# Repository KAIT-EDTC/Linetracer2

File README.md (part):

# Linetracer2 — 子ども向け教材ライントレーサー（Lite rev.L5）

> 最終更新: 2026-11-19（**Lite に一本化**。以前の「標準版 rev.A1」（Raspberry Pi Pico ＋ LBR-123F ×6）は削除した。git の履歴（コミット `3216870` まで）に残っている）
> 基板は **rev.L5**（2026-11-19: **回路を全部見直した**（§0）。車輪を止めたときにモータードライバの定格 2.0 A を超えないようにソフトでモーターを平均 1.6 V までに、売っていない昇降圧モジュール AE-TPS63802 を **AE-XC9306-5V0** に（向きをまちがえられない）、電池のばねが一瞬離れても XIAO が落ちないように **C2 470 µF**。1 台 約 ¥171 安く）。その前の rev.L4（2026-10-30）はモーターに力がかかると XIAO が落ちる問題を 5 V 昇降圧モジュールで直した版（§0b）。**未製造・未試作**。
> **KiCad のファイル（回路図・基板・Gerber・PDF・絵）、手順の絵、ロボット全体の 3D と干渉チェックは rev.L5 で作り直した**（KiCad 10.0.8、ERC 0・DRC 0（警告も 0）・未接続 0・回路図との不一致 0、干渉なし、2026-11-19）。
> マイコン **Seeed Studio XIAO ESP32C6**（ピンヘッダで付ける）、センサー **LBR-127HLD ×3**、モータードライバー **TC78H653FTG**（秋月モジュール）、**130 モーター ×2** と 3D プリントのギヤボックス（1 段 5:1）、**ブザー**、**フルカラー LED 6 こ**、**テストパッド**、XIAO 用の **5 V 昇降圧モジュール（AE-XC9306-5V0）**。配線は全部手で引いた（交差なし・ビア 0）。前の支えは**ボールキャスター**（§1）。
> **全部足付き部品（スルーホール）で子どもが自分ではんだ付けできる**。テープ・接着剤は使わず、M3 ねじと 3D プリントのツメで組み立てる。部品は秋月・ホームセンター・タミヤ品など、**T 番号のある店で買える定番品だけ**（`docs/bom.md` §0）。
> 回路図: `hardware/kicad/Linetracer2-Lite.kicad_sch`（PDF: `docs/Linetracer2-Lite_schematic.pdf`）
> 製造データ: `hardware/Linetracer2-Lite_rev.L5_gerber.zip`（発注のしかた §4.10。rev.L3・rev.L4 の Gerber は消した。git の履歴に残っている）　ソフト: `firmware/micropython/`（Arduino C++ 版: [`firmware/arduino/`](firmware/arduino/README.md)）　組み立て手順書: [`docs/assembly.md`](docs/assembly.md)
> **ロボット全体の 3D モデル**: `hardware/Linetracer2-Lite_assembly.stl`（GitHub 上でそのまま回して見られる）、色つき `hardware/Linetracer2-Lite_assembly.glb`。部品付き基板だけの STEP: `hardware/kicad/Linetracer2-Lite_pcb.step`
> 前の版 rev.L2（XIAO じか付け、自動配線）は git の履歴とプルリクエスト #3 に、rev.L1（Pico ＋ LBR-123F）はコミット `1db5a53` に残っている。

| ロボット全体（3D） | 横から |
|---|---|
|  |  |

| 基板の上面（3D） | 裏面（3D、センサー面） |
|---|---|
|  |  |

| シルク（表。子どもが読む印刷） | シルク（裏、下から見た向き） |
|---|---|
|  |  |

## ドキュメント

| ファイル | 内容 |
|---------|------|
| この README | 設計書（依頼と結論・変更点と理由・回路・基板・部品表・ソフト・作り直し方・まだ確かめていないこと） |
| [docs/assembly.md](docs/assembly.md) | 組み立て手順書（基板の記号の見かた、つくる順番 ①〜⑰、機械の組み立て、うごかしかた） |
| [docs/bom.md](docs/bom.md) | 部品表（秋月のリンクつき）、買い方のルール、10 台分の注文リスト |
| [docs/drivetrain.md](docs/drivetrain.md) | 駆動系の計算（モーター・ギヤ比・速さ・電流）と電池 |
| [docs/08_knowledge.md](docs/08_knowledge.md) | 知見メモ（部品のクセ、買い方、KiCad / OpenSCAD のハマりどころ、設計判断） |
| [hardware/mechanical/README.md](hardware/mechanical/README.md) | 3D プリント部品と P1S の印刷設定、ねじ、干渉チェック |
| [hardware/Linetracer2-Lite_print_set.zip](hardware/Linetracer2-Lite_print_set.zip) | 1 台分の STL を印刷設定ごとのフォルダに分けた zip |
| [docs/Linetracer2-Lite_schematic.pdf](docs/Linetracer2-Lite_schematic.pdf) | 回路図 PDF（組立図: `docs/Linetracer2-Lite_assembly_top.pdf` / `_bottom.pdf`） |
| [docs/datasheets/README.md](docs/datasheets/README.md) | 使った部品のデータシート（リンク集） |

## フォルダ構成

```
Linetracer2/
├── README.md                 設計書（このファイル）
├── docs/                     手順書・部品表・知見メモ、回路図/組立図 PDF、基板とロボットの画像、手順ごとの絵（steps/）
├── hardware/
│   ├── kicad/                KiCad 10 プロジェクト（Linetracer2-Lite.kicad_pro / _sch / _pcb）、自作ライブラリ（lib/）、BOM、ERC/DRC
│   ├── gerber/               製造用 Gerber・ドリル
│   ├── Linetracer2-Lite_rev.L5_gerber.zip   ← 基板メーカーにそのまま渡す
│   ├── Linetracer2-Lite_assembly.stl / .glb ロボット全体の 3D
│   ├── Linetracer2-Lite_print_set.zip       3D プリント 1 台分
│   └── mechanical/           3D プリント部品（OpenSCAD 元データ、STL、図）
├── firmware/
│   ├── micropython/          ライブラリ・標準プログラム・授業用サンプル（XIAO ESP32C6 用 MicroPython）
│   └── arduino/              Arduino（C++）版のライブラリとスケッチ
└── scripts/                  回路図・基板・3D モデルを作り直すスクリプト（§9）
```

---

## 0. rev.L5（2026-11-19）: 回路を全部見直した（落ちない・こわれない・安く）

依頼「モーターを最大で回したときなどに不具合が起きないか。いまの昇降圧（でんげん モジュール）で大丈夫か。もっと安くできないか（電池を 1 本増やすだけでも変わるかも）。落ちないようにする工夫。LED の抵抗の付け忘れや、電流を食いすぎてモーターの電圧が下がるような所がないか。子どもがフラフラ（ゆらす・つかむ・ぶつける）してもマイコンがプツンと落ちない、電子回路として正しく動く、いらない部品は削ってよい、いちばん安全で、値段もおさえた回路に」への答え。

**結論**: 回路の形（電池 3 本 → モーター、電池 → D1 → 5 V 昇降圧 → D8 → XIAO）はそのままでよい。直すべき所が 3 つあった: **① 車輪を止めるとドライバの定格を超える電流が流れる**（ソフトの上限で直した）、**② でんげん モジュールが売っていない**（同じ働きで安く、向きをまちがえられないモジュールに替えた）、**③ 電池のばねが一瞬離れると XIAO が落ちる**（電気だめのコンデンサを足した）。1 台 **約 ¥171 安く**なった（約 ¥3,360）。電池を 4 本にする案は、かえって落ちやすく高くつくのでやめた（§0.4）。

### 0.1 見つかったことと、したこと

| # | 見つかったこと | どうなるか | rev.L5 |
|---|---|---|---|
| 1 | **モーターの「100 %」は平均 3.0 V。車輪を手で止める・壁に当たると約 2.6 A**（止まったモーターは逆起電力が無く、電流 = 電圧 ÷ 約 0.9 Ω）。ドライバ TC78H653FTG（スモールモード）の**絶対最大定格は 2.0 A**（10 ms までなら 2.5 A）。過電流検出（ISD）のしきい値はデータシートでも「参考値・保証しない」（VM 3〜4 V で 2〜3 A）ので、**働かないまま 2.0〜3 A が流れ続ける**ことがある。ソフトは 0.1 秒ごとに ISD を解除するので、止めている間ずっとくり返す | ドライバがこわれる・熱くなる。モーターも 4.6 W で熱くなる。電池が 2.5 V まで下がる | **ソフトの上限 `MAX_MOTOR_VOLT` を 3.0 → 1.6 V**（MicroPython・Arduino とも）。止めても**最大約 1.75 A**（定格の 9 割弱）。**電池から出る電流も半分**になり、電池の電圧の落ちこみも半分。速さは理論 2.7 m/s で十分（3 センサーで実際に走れるのは 1 m/s 前後）。速さレベルと Kp・Kd を合わせ直した（`docs/drivetrain.md` §3） |
| 2 | **でんげん モジュール AE-TPS63802 が秋月で「入荷未定」、店も通販も在庫 0**（2026-11-19。値段も 2026-01 に ¥660 → ¥780）。さらに、VR1 の代わりの 470 kΩ を付ける前に電気を入れると**こわれる**準備が要り、4 ピン 1 列なので**裏返しでも差さる** | 授業の 10 台がそろわない。先生の準備でこわしやすい | **AE-XC9306-5V0（秋月 115775、¥600、在庫 386）に替えた**。同じ同期整流の昇降圧で **5 V 固定**（入力 2.5〜5.5 V、3.3 V 入力で 500 mA）。準備は付属の細ピンヘッダを付けて **TRIM のピンを 1 本抜くだけ**。**基板に TRIM の穴を開けない**ので、モジュールは**正しい向きでしか入らない**（裏返しても回しても入らない → 入力と出力を入れかえられない）。20 × 13 mm → 8.5 × 7.6 mm |
| 3 | 電池ボックスのばねは、ぶつけたりゆらしたりすると**一瞬（〜数 ms）離れる**。VSYS（= USB の VBUS）は USB の決まり（10 µF まで）で大きいコンデンサを置けず、電気だめが 40 µF ほどしかない（0.5 ms） | 子どもがゆらす・ぶつけると XIAO が「プツン」とリセットしうる | **C2 470 µF を D1 のうしろ（モジュールの入力 VIN_BB）に足した**。D1 があるのでモーターには吸われず、USB の VBUS でもない。約 3 ms もつ（モジュールは 2.5 V まで動く）。**C1 と同じ部品**で、⑮ でいっしょに付ける（部品の種類は増えない、+¥10） |
| 4 | フルカラー LED は明るさ 255 で 6 こ 0.36 A。**XIAO の Wi-Fi の次に 5 V を食う**。子どもがソフトで 255 にすると、電池が減ったときにモジュールの出せる電流（2.5 V 入力で約 0.3 A）が足りなくなる | 電池が減ると XIAO が落ちる | ソフトで明るさを**最大 100（6 こ白で 0.14 A）に固定**（`RGB_LIMIT`、MicroPython・Arduino。標準は今までどおり 60） |
| 5 | **LED の抵抗の付け忘れ** | — | **無かった**。赤外 LED（センサーの中）は 100 Ω で約 20 mA（最大 60 mA）。フルカラー LED は中に定電流回路があるので抵抗は要らない（R11 は信号線の保護、§3.6）。XIAO の LED は XIAO の中で抵抗付き。トランジスタのベース（R7 1 kΩ）・ブザー（R9 100 Ω）・ボタン（R10 1 kΩ）も OK |
| 6 | **電流を食いすぎて、モーターの電圧を下げている所** | — | **無かった**（§0.3）。モーター以外は全部で電池から 0.15〜0.7 A（Wi-Fi のとき多い）。モーターの電圧が下がる原因は電池の内部抵抗とモーター自身の電流（1 で半分にした） |
| 7 | 電池を逆に付ける（J1 を逆にはんだ付け）と、ドライバの中のダイオードで電池がショート | ドライバがこわれる・電池が熱くなる | 変わらず（足付きで 3 V で ON する MOSFET が秋月に無い、PTC は止めたときの電流で切れる・電圧が下がる）。**XH コネクタは逆に差せない形**、手順書 ⑩ で先生が向きを見る。D1 が XIAO とモジュールは守る |
| 8 | 手順の絵を作る `scripts/step_images.py` が、Lite をリポジトリの直下に移したあとも古い場所（`lite/docs/steps`）に書こうとして失敗していた（`export_assembly.sh` のパイプで失敗が隠れていた） | 手順の絵・3D が古いまま | 直して、失敗が隠れないようにした。**手順の絵・ロボット全体の 3D・干渉チェックを rev.L5 で作り直した**（rev.L3 のままだった） |

**いらない部品**: **470 kΩ（U3 の準備用）がいらなくなった**。ほかの部品はどれも役目がある（§0.5）ので残した。

### 0.2 モーターを止めたとき、電池の電圧はどこまで下がるか（計算）

電池（新品アルカリ 3 本: 4.7 V・0.7 Ω（ばね・スイッチ・線をふくむ）、半分使ったアルカリ: 3.8 V・1.0 Ω、ニッケル水素: 3.9 V・0.35 Ω）、モーター＋ドライバ 0.9 Ω、XIAO などの 5 V 側 0.1 A（Wi-Fi なし）、D1 0.35 V。

| 電池 | 場面 | rev.L4（上限 3.0 V、TPS63802 は 1.3 V まで） | **rev.L5（上限 1.6 V、XC9306 は 2.5 V まで）** |
|---|---|---|---|
| 新品アルカリ | 片方の車輪を止める | 電池 3.3 V・**モーター 2.6 A（定格超え）** | 電池 4.1 V・モーター 1.75 A |
| 新品アルカリ | 両方止める（走り出しの一瞬も近い） | 電池 2.5 V・モーター 2.0 A | 電池 3.7 V・モーター 1.6 A |
| 新品アルカリ | 両方止める＋Wi-Fi（0.3 A） | 電池 2.3 V | 電池 3.5 V（モジュールの入力 3.2 V） |
| ニッケル水素 | 片方を止める | 電池 3.2 V・**モーター 2.5 A（定格超え）** | 電池 3.6 V・モーター 1.5 A |
| ニッケル水素 | 両方止める＋Wi-Fi | 電池 2.6 V・**モーター 2.1 A（定格超え）** | 電池 3.3 V（入力 3.0 V） |
| 半分使ったアルカリ | 片方を止める | 電池 2.2 V（入力 1.9 V で動く） | 電池 3.1 V（入力 2.7 V で動く） |
| 半分使ったアルカリ | 両方止める | 電池 1.6 V（入力 1.2 V → **XIAO が落ちる**） | 電池 2.7 V（入力 2.3 V → **XIAO が落ちる**） |

- rev.L5 は**新品アルカリ・ニッケル水素なら、両輪を止めても、Wi-Fi を使っていても落ちない**。どの場面でもドライバの定格 2.0 A を超えない。
- 半分使ったアルカリで両輪を止めると、rev.L4 と同じく落ちる（モジュールが止まる → XIAO がリセット → モーターも止まって電流が減る → 電池がもどってまた起動し、ド・ミ・ソが鳴る）。**電池を替えるサイン**。こわれはしない。
- **いちばん落ちにくいのはニッケル水素（eneloop など）**（内部抵抗が小さい）。`BATTERY_VOLT` を 3.7 に（§8.2）。
- 計算のしかた: モーターの電流 = デューティ × 電池の電圧 ÷ 0.9 Ω、電池の電流 = デューティ × モーターの電流 ＋ 5 V 側（5 V × 電流 ÷ 効率 0.85 ÷ 入力の電圧）、電池の電圧 = 開放電圧 − 内部抵抗 × 電池の電流（くり返し計算）。デューティはソフトが `MAX_MOTOR_VOLT ÷ BATTERY_VOLT`（4.2 V）で決める（電池を測れないので）。

### 0.3 どこが電流を使うか

| 使う所 | 電流 | 電源 |
|---|---|---|
| モーター 2 こ | 走っている間 1 こ 0.2〜0.7 A（電池からは合わせて 0.3〜1 A）。止めると最大 1.75 A（rev.L5） | VBAT（電池そのまま） |
| フルカラー LED 6 こ | 1 こ 待機 約 1 mA、白でいっぱいに光ると 60 mA。標準の明るさ 60/255 で 6 こ白 約 85 mA、上限 100 で 0.14 A | VSYS（5 V 側） |
| 赤外 LED 3 こ（センサー） | 20 mA × 3 = 60 mA（読むときだけ ON、外の光を消すため ON/OFF をくり返す） | 3V3（XIAO の中の降圧） |
| XIAO（ESP32-C6） | 走るだけ 約 30 mA、Wi-Fi の電波を出す瞬間 約 0.3 A | 3V3 |
| センサーのプルアップ・ボタン・ブザー | 1 mA 以下（ブザーは鳴っている間 数 mA） | 3V3 / D4 |
| **でんげん モジュール（U3）が出す 5 V** | **0.1 A（走るだけ）〜 0.4 A（Wi-Fi ＋ LED）**。出せるのは 3.3 V 入力で 0.5 A（秋月の資料、基板にじか付けのとき）。電池側では 0.15〜0.7 A | VIN_BB（D1 のあと） |

- XIAO の 3V3 は XIAO の中の降圧 DC-DC（SGM6029）が作る。赤外 LED 60 mA ＋ ESP32-C6 で十分まにあう。
- **ピンの電流**: どの GPIO も 5 mA 以下（ドライバの入力 µA、Q1 のベース 2.6 mA、ブザー 33 mA は R9 で決まる瞬間のピークで、ふだん数 mA、R11 は 5 mA 以下）。ESP32-C6 の限度（40 mA / 28 mA）の中。

### 0.4 電池を 4 本にしたら？（答え: しない）

| | 単3 ×3（いま） | 単3 ×4 |
|---|---|---|
| 電池の電圧 | 3.3〜4.8 V | 4.4〜6.4 V |
| XIAO の電源 | 5 V 昇降圧モジュールが要る（電池が 3.8 V を切ると、ダイオードだけでは XIAO が動かない） | **それでも電源の部品が要る**: XIAO の 5V ピン（= USB の VBUS）は **5.6 V でクランプ**される（Seeed の回路図）。新品アルカリ 4 本 6.4 V は高すぎ、いまのモジュール（5.5 V まで）にも入れられない → 降圧（LDO など）が要る |
| 落ちにくさ | 電池が 2.8 V まで下がっても XIAO は動く | LDO だと電池が**約 4.5 V を切ると XIAO が落ちる**（LDO の電圧降下 0.3〜0.5 V ＋ D8 ＋ XIAO の中の降圧）。半分使ったアルカリ 4 本（5.0 V・1.2 Ω）で両輪を止めると 3.9 V → **落ちる**。いまより落ちやすい |
| 部品代 | AE-XC9306-5V0 ¥600 | 低損失 LDO 50〜100 円（−¥500）。でも電池ボックス（4 本）、**デッキの作り直し**、重さ +23 g |
| 電池代 | 1 回 3 本 | 1 回 4 本（授業 10 台で毎回 +10 本） |
| モーター | — | 電圧が高い分デューティが小さくなるだけ。止めたときの電流はソフトの上限で決まるので同じ |
| 間違い | — | 子どもが 4 本のボックスに替えたまま古い基板（rev.L4 以前）を使うとこわれる |

→ 4 本にしても電源の部品は要り、落ちにくさは悪くなり、機械の作り直しと電池代が増える。**3 本＋昇降圧のまま**にした。

### 0.5 もっと安くできるか・部品を減らせるか

| 案 | 差 | 判断 |
|---|---|---|
| **でんげん モジュールを AE-XC9306-5V0 に** | −¥180（470 kΩ も不要） | **した**（§0.1 の 2） |
| C2 470 µF を足す | +¥10 | **した**（§0.1 の 3、落ちない工夫） |
| もっと安い昇圧モジュール（秋月 AE-XCL102D503CR-G ¥300 など） | −¥300 | しない。出力 0.21 A で、Wi-Fi（0.3 A の瞬間）や LED で足りない |
| マイコンを Raspberry Pi Pico 2 W に（中に 1.8〜5.5 V の昇降圧があり、電池の電圧も測れる） | XIAO ¥1,100 ＋ モジュール ¥600 → Pico 2 W 約 ¥1,500（スイッチサイエンス）で −¥200 くらい | 今回はしない。基板・ソフト（MicroPython・Arduino・Wi-Fi）を全部作り直すことになる。Wi-Fi が要らなければ Wi-Fi なしの Pico でもっと安くなる。次の世代の候補 |
| フルカラー LED を 6 → 2 こ | −¥160 | しない（依頼で 6 こにした） |
| D9・R11・C3・C4・テストパッドをやめる | −¥1〜20 | しない。D9 = LED が XIAO の 3.3 V の信号を読むため、R11 = はんだのミスで XIAO のピンがこわれないため、C3・C4 = モーターの雑音（センサー・Wi-Fi）、テストパッド = 銅だけで 0 円 |
| D1 をやめる | −¥10 | しない。電池の逆接続から XIAO とモジュールを守り、C2 をモーターから切りはなす |
| D8 をやめる | −¥10 | しない。無いと USB をつないだとき、モジュールと PC の USB が 5 V を押しあう |

### 0.6 回路（rev.L5）

```
単3×3 ─ VBAT ─┬─ モータードライバ VM（C1 470µF）。モーターは平均 1.6 V まで（ソフト）
              └─ D1 1N5819 ─ VIN_BB ─┬─ C2 470µF（電気だめ。ばねが一瞬離れても約 3 ms もつ）
                                      └─ U3 AE-XC9306-5V0（昇降圧 5.0 V、ON/OFF は空き、TRIM は穴なし）
                                           └─ VOUT_BB ─ D8 1N5819 ─ VSYS（約 4.7 V）─┬─ XIAO 5V ピン → 3.3 V
                                                                                      ├─ 右のフルカラー LED 3 こ
                                                                                      └─ D9 1N4148 ─ VLED_L（約 4.0 V）─ 左の 3 こ
              USB-C の 5 V も VSYS に来る（XIAO の中で直結）。D8 があるので U3 には流れない
```

- 配置: U3 は真ん中（rev.L4 の大きいモジュールの場所の後ろ半分）。左の列 = I（前）・G・O（うしろ）、右の列 = ON/OFF・GND・（TRIM の穴なし）。**O は D8 のアノードと同じ高さ**で 1 本の横線、**C2 の ＋ は U3 の I のまっすぐ前**で、D1 → C2 ＋ → U3 I が 1 本の線。抵抗の絵（① ちゃ ② だいだい ③ あか）は C2 の右、XIAO のアンテナの前へ移した（銅の禁止エリアだがシルクは描ける）。U3 の下には線を通さない。
- **U3 の外形とピンの位置は秋月の説明書の図から**（8.5 × 7.6 mm、ピッチ 2.54、列の間 7.6）。図の向き（裏から見たか表から見たか）を読みちがえていても、TRIM の穴が無いので「部品の面を下にした向き」でだけ入り、どのピンも正しい穴に来る。**発注の前に実物で確かめる**（§10）。
- KiCad で作り直した: ERC 0、**DRC 0（警告も 0）**、未接続 0、回路図との不一致 0（KiCad 10.0.8）。Gerber は `hardware/Linetracer2-Lite_rev.L5_gerber.zip`（rev.L4 の zip は消した）。ロボット全体の 3D と干渉チェック（`export_assembly.sh`）も rev.L5 で通した: 枠・デッキ・電池ボックス・モーター・ギヤ・キャスター・ねじ、すべて「空」。
- ソフト: MicroPython は構文チェック、Arduino は 3 つのスケッチを XIAO_ESP32C6 用にコンパイルした（esp32 3.3.11）。**実物ではまだ動かしていない**。

### 0.7 部品とコスト（1 台）

| | 変化 |
|---|---|
| U3 AE-TPS63802（¥780）→ **AE-XC9306-5V0（115775、¥600）** | −¥180 |
| 470 kΩ（VR1 の代わり）をやめた | −¥1 |
| **C2 470 µF**（C1 と同じ 108426） | +¥10 |
| **合計** | **−¥171 → 1 台 約 ¥3,360**（rev.L4 約 ¥3,531） |

はんだ付けは子どもが +3 か所（U3 は 4 → 5、C2 の 2）、先生の準備は 6 → 5 か所（細ピンヘッダ 5、抵抗なし）。

---

## 0b. rev.L4（2026-10-30）: モーターに力がかかると XIAO が落ちる → 電源を作り直した

> rev.L4 のときの記録。**rev.L5 で U3 は AE-XC9306-5V0 に替わり（470 kΩ の準備は不要）、C2 470 µF を D1 のうしろに足し、モーターの上限を 1.6 V にした**（§0）。下の U3 の説明・部品・コストは rev.L4 の AE-TPS63802 のもの。

依頼「モーターにトルクをかけたときや、モーター出力 100 % にしたときに XIAO が落ちるので回路を組み直して。ほかにも回路的に良くないところ・問題点をくまなく見て」への答え。

### 0b.1 原因: XIAO の電源が、モーターと同じ電池から「ダイオード 1 本」でとっていた

rev.L3 は `単3×3 ─ D1 ─ XIAO の 5V ピン` だった。XIAO の中は `5V ピン ─ ショットキー（約 0.3 V）─ 降圧 DC-DC ─ 3.3 V` なので、3.3 V を保つには電池の側で**約 4.0 V**、ESP32-C6 がリセットしないためにも**約 3.4 V** 要る。ところが単3 アルカリ 3 本は、モーターが大きい電流を流すとすぐその下まで下がる。

計算の前提: 電池 3 本 ＋ 電池ボックスのばね・スイッチ・線の抵抗 ≒ 0.7 Ω（新品）、FA-130RA-2270 の巻線 ≒ 0.68 Ω（1.5 V で止めると 2.2 A）、TC78H653FTG（スモールモード）のオン抵抗 0.22 Ω、ソフトの 100 % = 電池の 71 %（3.0 V ÷ 4.2 V）。

| 場面 | 電池から出る電流 | 電池の電圧（新品 4.65 V） | rev.L3 の XIAO |
|---|---|---|---|
| ふつうに走っている（2 つで 1 A くらい） | 約 1.0 A | 約 3.9 V | ぎりぎり動く |
| **片方の車輪を手で止めて 100 %**（もう片方は止まっている） | 約 1.9 A | **約 3.3 V** | **リセット** |
| **2 つとも 100 % で走り出す・2 つとも止める** | 約 2.9 A | **約 2.6 V** | **リセット** |
| （少し減った電池 3.9 V・1.2 Ω で 2 つとも止める） | 約 1.9 A | 約 1.7 V | リセット |

- 470 µF（C2）は 0.2 A で 1 ms ほどしか持たない。モーターが止まっている間（何百 ms）は支えられない。
- つまり**ソフトの問題ではなく、電源の作り方の問題**。走り出しのソフトスタート（`RAMP_PER_CALL`）は入っているが、車輪を止められると電流は減らない。
- 標準版（Pico）では起きにくい: Pico の VSYS の中に**昇降圧の DC-DC（1.8〜5.5 V）**があるから。XIAO ESP32C6 の中は降圧だけなので、Lite では外に昇降圧が要る。

### 0b.2 なおしかた: XIAO 専用の 5 V を、昇降圧モジュールで作る

```
単3×3 ─ VBAT ─┬─ モータードライバ VM（C1 470µF）
              └─ D1 1N5819 ─ VIN_BB ─ U3 AE-TPS63802（昇降圧、VR1 = 470kΩ → 5.13 V、EN = VIN）
                                        └─ VOUT_BB ─ D8 1N5819 ─ VSYS（約 4.8 V）─┬─ XIAO 5V ピン → 3.3 V
                                                                                   ├─ 右のフルカラー LED 3 こ（D5〜D7）
                                                                                   └─ D9 1N4148 ─ VLED_L（約 4.1 V）─ 左の 3 こ（D2〜D4）
              USB-C の 5 V も VSYS に来る（XIAO の中で直結）。D8 があるので U3 には流れない
```

- **U3 = 秋月 AE-TPS63802**（TI TPS63802 の昇降圧モジュールキット、¥780、20 × 13 mm、4 ピン: VIN・GND・VOUT・EN）。**入力 1.3〜5.5 V で動き続け**（はじめの起動は 1.8 V 以上）、スイッチ電流 2 A。電池が**約 1.6 V**（D1 のあとで 1.3 V）まで下がっても XIAO に 5 V を出す。上の表のいちばん悪い場面（2.6 V）でも余裕がある。
  - 昇圧だけでなく**昇降圧**なので、新品のアルカリ（4.8 V）でもニッケル水素（3.6 V）でも同じ 5.13 V。
  - 秋月で買えて、ピンヘッダで付けられて、1 A 近く出せるのはこれだけだった。もっと安い昇圧モジュール（AE-XCL102 / XCL103、5 V）は出力 0.2 A ほどで、Wi-Fi（`03_WiFiControl`）やフルカラー LED を使うと足りない。
  - 出力は VR1（25 回転の半固定抵抗）で決まる。**VR1 の代わりに 470 kΩ の抵抗を付けて 5.13 V に固定**（秋月の説明書の表の値。半固定抵抗だと回してしまう・高さがある）。**VR1 が空のまま電気を入れるとこわれる**ので、先生が先に付けて単3 ×2 本でためす（手順書 §0）。
  - EN は VIN につないで「いつも ON」（TI の注意: EN を浮かせてはいけない）。モードのジャンパーはそのまま（強制 PWM）。
- **D8**（1N5819）: XIAO の 5V ピンは USB の VBUS と直結。D8 が無いと、U3 が PC の USB に電気を押しこみ、USB の 5 V が U3 の出力に逆から入る。D8 のおかげで VSYS は約 4.8 V（USB の 5 V より少し低い）: **USB をつなぐと USB から、外すとすぐ U3 から**。
- **D1**（1N5819）はそのまま: 電池を逆につないだとき、U3 と XIAO を守る（U3 の入力は −0.3 V まで）。
- **C2（VSYS の 470 µF）はやめた**: VSYS は USB の VBUS そのもので、USB の決まりは 10 µF まで（差した瞬間の突入電流で PC のポートが落ちることがある）。U3 の出力にはモジュールのコンデンサがある。
- XIAO の 5V ピンには約 4.8 V。中の降圧 DC-DC にとって十分（3.6 V 以上あればよい）。

### 0b.3 ほかに見つけた回路の問題と対応

| # | 問題 | どうなるか | rev.L4 |
|---|---|---|---|
| 1 | **XIAO の電源が電池じか**（§0b.1） | モーターに力がかかると XIAO がリセット | **U3（5 V 昇降圧）を足した** |
| 2 | **ニッケル水素 3 本（3.6 V）だと、止まっていても足りない**（rev.L3 の説明は「NiMH は `BATTERY_VOLT` を 3.7 に」としていたが、XIAO の 3.3 V が保てない） | 不安定・動かない | U3 で解決（NiMH でも 5.13 V。内部抵抗が小さいのでモーターにはむしろよい） |
| 3 | **USB の VBUS（= VSYS）に 470 µF（C2）** | USB を差した瞬間の突入電流（規格は 10 µF まで）。PC のポートが落ちる・つながらないことがある | C2 をやめた（部品が 1 つ減った） |
| 4 | **フルカラー LED の信号の電圧が足りない**: PL9823 は VDD の 0.7 倍より高いと「1」。USB の 5 V では 3.5 V 要るが、XIAO は 3.3 V | USB だけだと光らない・色がおかしい（rev.L3 §10 で心配していたこと）。U3 で VSYS が 4.8 V に上がると電池でも同じになる | **左の 3 こ（信号が最初に入る D2 を含む）の電源を D9（1N4148）で 0.7 V 下げた**: 約 4.1 V → 2.9 V で「1」。D2〜D4 は自分の VDD（4.1 V）で次へ信号を渡すので、右の 3 こ（4.8 V → 3.4 V）にも足りる |
| 5 | フルカラー LED の電源が電池 − D1（新品で約 4.2 V）で、決まり（4.5〜6 V）より低い | 電池が減ると青と緑が暗くなる | 右の 3 こは 4.8 V（決まりの中）。左の 3 こは 4.1 V（rev.L3 と同じくらい、でも電池が減っても変わらない） |
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
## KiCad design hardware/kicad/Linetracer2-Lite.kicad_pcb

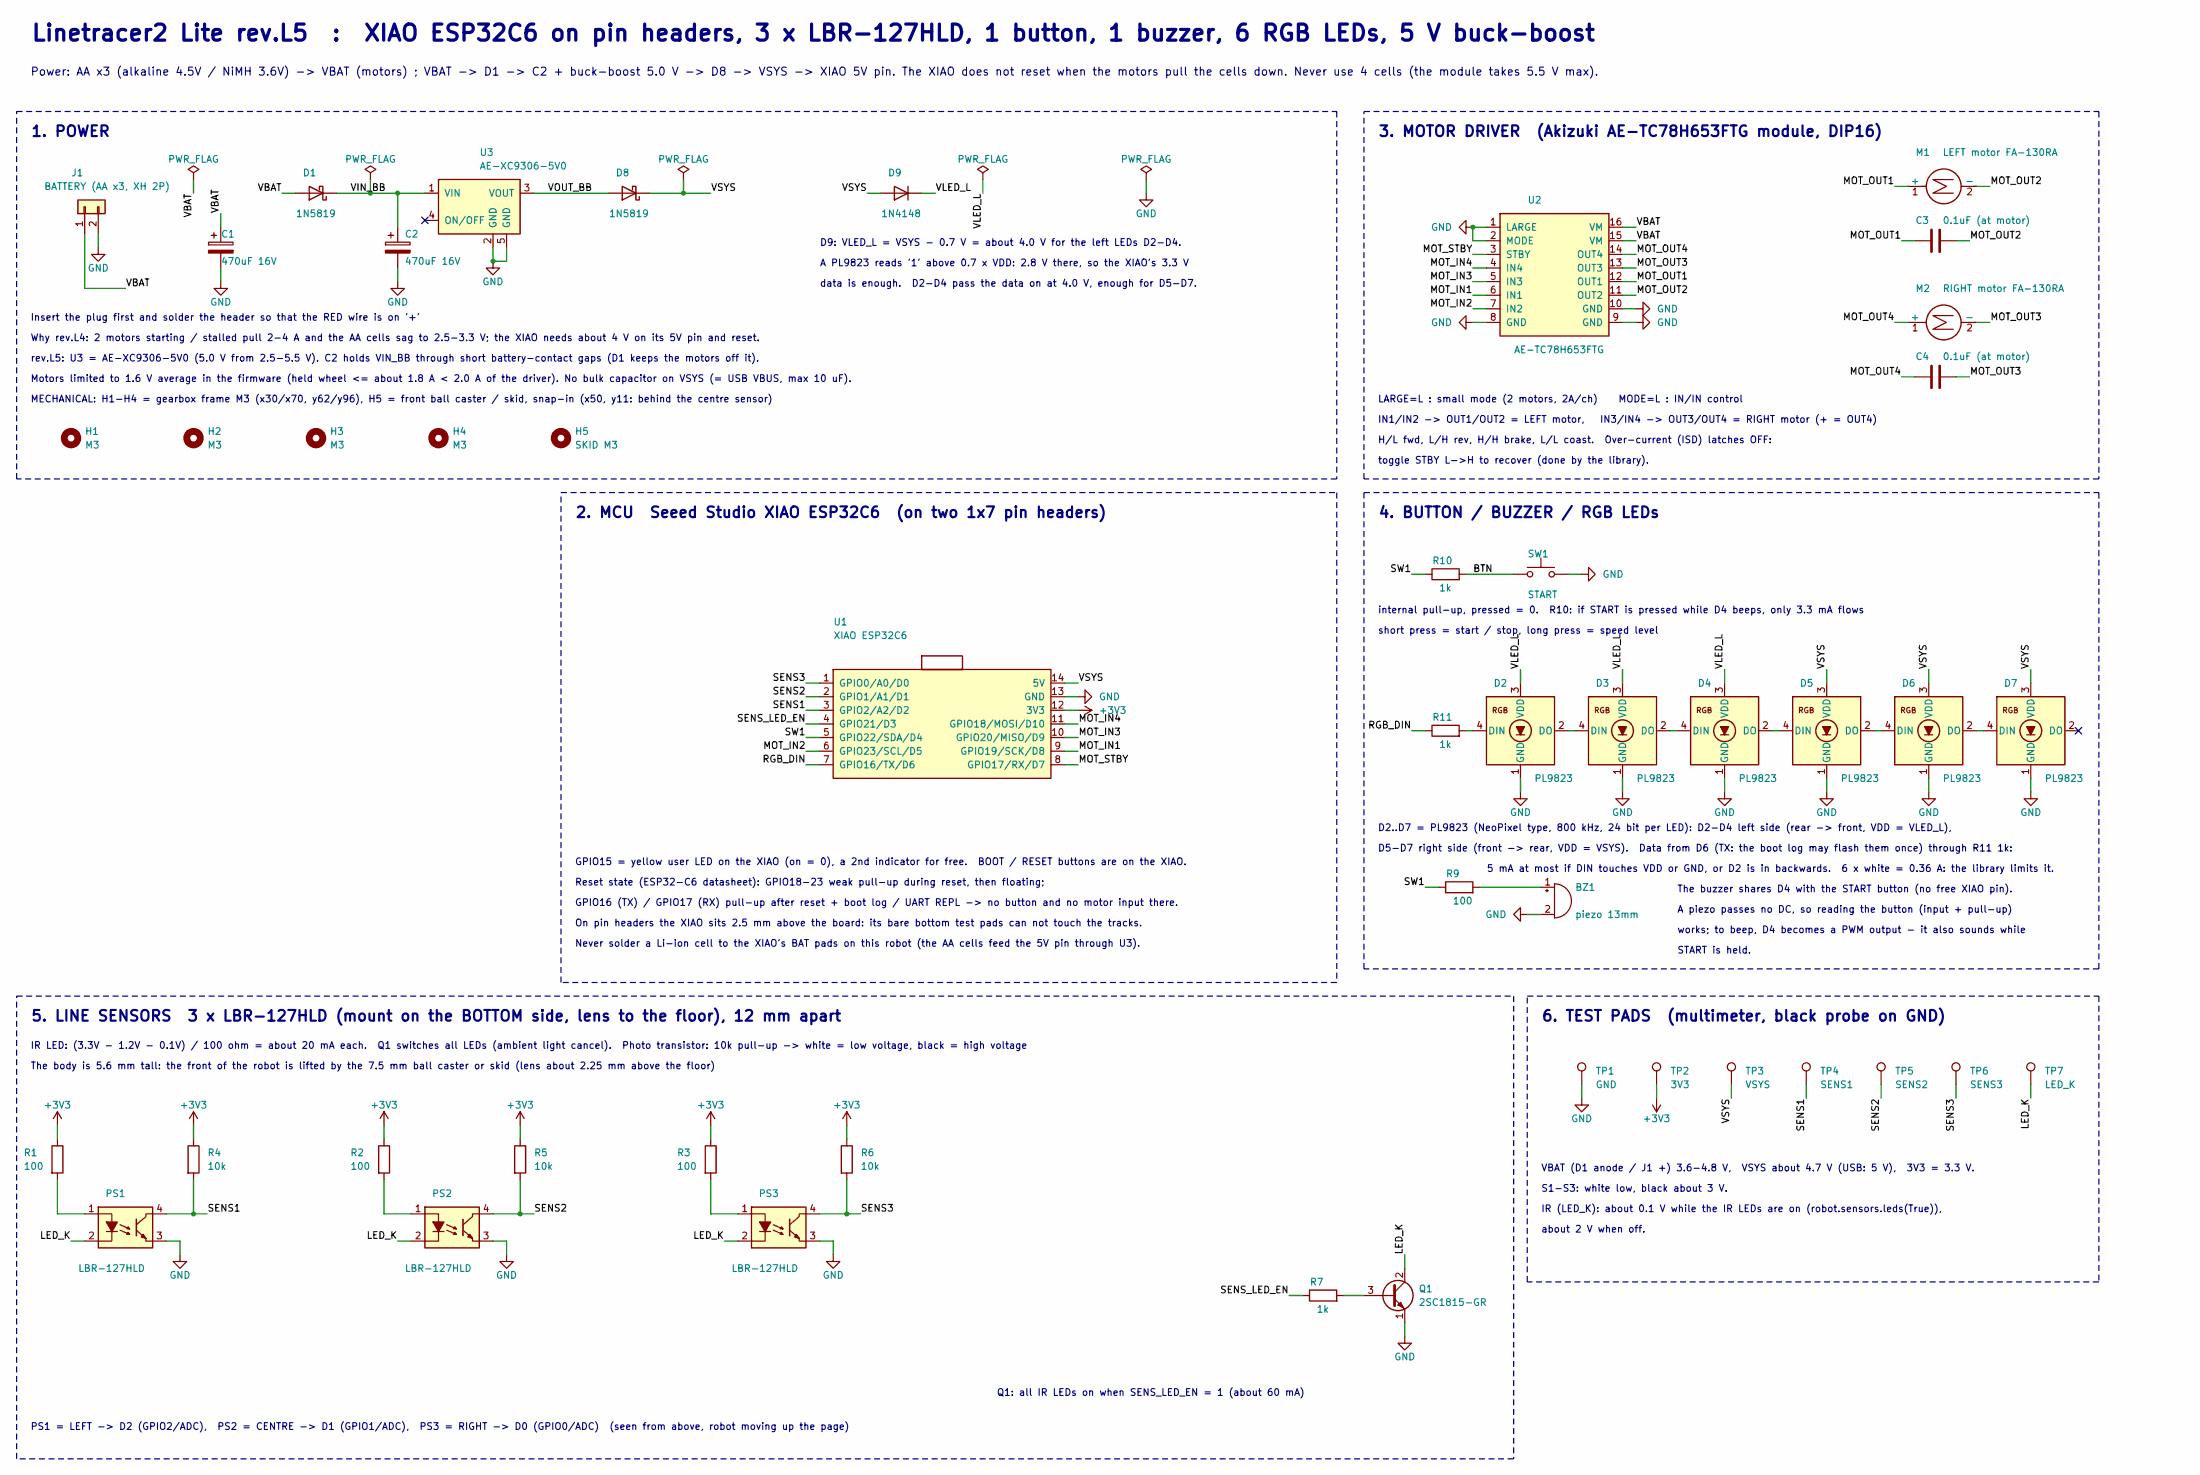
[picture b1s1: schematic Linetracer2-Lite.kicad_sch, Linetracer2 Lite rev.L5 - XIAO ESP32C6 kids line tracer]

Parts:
BZ1: piezo 13mm; Buzzer_PKM13_P5.0
C1, C2: 470uF 16V; CP_Radial_D8.0mm_P3.50mm
C3, C4: 0.1uF (at motor); C_Disc_D3.0mm_W2.0mm_P2.50mm
D1, D8: 1N5819; D_DO-41_SOD81_P7.62mm_Horizontal
D2, D3, D4, D5, D6, D7: PL9823; LED_PL9823_5mm
D9: 1N4148; D_DO-35_SOD27_P7.62mm_Horizontal
H1, H2, H3, H4: M3; MountingHole_3.2mm_M3
H5: SKID M3; MountingHole_3.2mm_M3
J1: BATTERY (AA x3, XH 2P); BatteryXH_2P
M1: LEFT motor FA-130RA; MotorPads_2P_Relief
M2: RIGHT motor FA-130RA; MotorPads_2P_Relief
PS1, PS2, PS3: LBR-127HLD
Q1: 2SC1815-GR; TO-92_Inline_Wide
R1, R2, R3, R9: 100; R_Axial_DIN0207_L6.3mm_D2.5mm_P10.16mm_Horizontal
R4, R5, R6: 10k; R_Axial_DIN0207_L6.3mm_D2.5mm_P10.16mm_Horizontal
R7, R10, R11: 1k; R_Axial_DIN0207_L6.3mm_D2.5mm_P10.16mm_Horizontal
SW1: START; SW_PUSH_6mm
TP1: GND; TestPoint_Pad_D1.5mm
TP2: 3V3; TestPoint_Pad_D1.5mm
TP3: VSYS; TestPoint_Pad_D1.5mm
TP4: SENS1; TestPoint_Pad_D1.5mm
TP5: SENS2; TestPoint_Pad_D1.5mm
TP6: SENS3; TestPoint_Pad_D1.5mm
TP7: LED_K; TestPoint_Pad_D1.5mm
U1: XIAO ESP32C6; XIAO_ESP32C6_Header
U2: AE-TC78H653FTG
U3: AE-XC9306-5V0

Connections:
+3V3: R1.1, R2.1, R3.1, R4.1, R5.1, R6.1, TP2.1, U1.12 (3V3)
/BTN: R10.2, SW1.1
/LED_K: PS1.2 (K), PS2.2 (K), PS3.2 (K), Q1.2 (C), TP7.1
/MOT_IN1: U1.9 (GPIO19/SCK/D8), U2.6 (IN1)
/MOT_IN2: U1.6 (GPIO23/SCL/D5), U2.7 (IN2)
/MOT_IN3: U1.10 (GPIO20/MISO/D9), U2.5 (IN3)
/MOT_IN4: U1.11 (GPIO18/MOSI/D10), U2.4 (IN4)
/MOT_OUT1: C3.1, M1.1 (+), U2.12 (OUT1)
/MOT_OUT2: C3.2, M1.2 (-), U2.11 (OUT2)
/MOT_OUT3: C4.2, M2.2 (-), U2.13 (OUT3)
/MOT_OUT4: C4.1, M2.1 (+), U2.14 (OUT4)
/MOT_STBY: U1.8 (GPIO17/RX/D7), U2.3 (STBY)
/RGB_DIN: R11.1, U1.7 (GPIO16/TX/D6)
/SENS1: PS1.4 (C), R4.2, TP4.1, U1.3 (GPIO2/A2/D2)
/SENS2: PS2.4 (C), R5.2, TP5.1, U1.2 (GPIO1/A1/D1)
/SENS3: PS3.4 (C), R6.2, TP6.1, U1.1 (GPIO0/A0/D0)
/SENS_LED_EN: R7.1, U1.4 (GPIO21/D3)
/SW1: R9.1, R10.1, U1.5 (GPIO22/SDA/D4)
/VBAT: C1.1, D1.2 (A), J1.1, U2.15 (VM), U2.16 (VM)
/VIN_BB: C2.1, D1.1 (K), U3.1 (VIN)
/VLED_L: D2.3 (VDD), D3.3 (VDD), D4.3 (VDD), D9.1 (K)
/VOUT_BB: D8.2 (A), U3.3 (VOUT)
/VSYS: D5.3 (VDD), D6.3 (VDD), D7.3 (VDD), D8.1 (K), D9.2 (A), TP3.1, U1.14 (5V)
GND: BZ1.2 (-), C1.2, C2.2, D2.1 (GND), D3.1 (GND), D4.1 (GND), D5.1 (GND), D6.1 (GND), D7.1 (GND), J1.2, PS1.3 (E), PS2.3 (E), PS3.3 (E), Q1.1 (E), SW1.2, TP1.1, U1.13 (GND), U2.1 (LARGE), U2.2 (MODE), U2.8 (GND), U2.9 (GND), U2.10 (GND), U3.2 (GND), U3.5 (GND)
unnamed: BZ1.1 (+), R9.2
unnamed: D2.4 (DIN), R11.2
unnamed: D2.2 (DO), D3.4 (DIN)
unnamed: D3.2 (DO), D4.4 (DIN)
unnamed: D4.2 (DO), D5.4 (DIN)
unnamed: D5.2 (DO), D6.4 (DIN)
unnamed: D6.2 (DO), D7.4 (DIN)
unnamed: PS1.1 (A), R1.2
unnamed: PS2.1 (A), R2.2
unnamed: PS3.1 (A), R3.2
unnamed: Q1.3 (B), R7.2

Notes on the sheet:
Q1: all IR LEDs on when SENS_LED_EN = 1 (about 60 mA)
D5-D7 right side (front -> rear, VDD = VSYS). Data from D6 (TX: the boot log may flash them once) through R11 1k:
short press = start / stop, long press = speed level
D9: VLED_L = VSYS - 0.7 V = about 4.0 V for the left LEDs D2-D4.
about 2 V when off.
3. MOTOR DRIVER (Akizuki AE-TC78H653FTG module, DIP16)
Power: AA x3 (alkaline 4.5V / NiMH 3.6V) -> VBAT (motors) ; VBAT -> D1 -> C2 + buck-boost 5.0 V -> D8 -> VSYS -> XIAO 5V pin. The XIAO does not reset when the motors pull the cells down. Never use 4 cells (the module takes 5.5 V max).
A PL9823 reads '1' above 0.7 x VDD: 2.8 V there, so the XIAO's 3.3 V
works; to beep, D4 becomes a PWM output - it also sounds while
IR (LED_K): about 0.1 V while the IR LEDs are on (robot.sensors.leds(True)),
START is held.
The buzzer shares D4 with the START button (no free XIAO pin).
5 mA at most if DIN touches VDD or GND, or D2 is in backwards. 6 x white = 0.36 A: the library limits it.
Insert the plug first and solder the header so that the RED wire is on '+'
Motors limited to 1.6 V average in the firmware (held wheel <= about 1.8 A < 2.0 A of the driver). No bulk capacitor on VSYS (= USB VBUS, max 10 uF).
MECHANICAL: H1-H4 = gearbox frame M3 (x30/x70, y62/y96), H5 = front ball caster / skid, snap-in (x50, y11: behind the centre sensor)
VBAT (D1 anode / J1 +) 3.6-4.8 V, VSYS about 4.7 V (USB: 5 V), 3V3 = 3.3 V.
S1-S3: white low, black about 3 V.
6. TEST PADS (multimeter, black probe on GND)
toggle STBY L->H to recover (done by the library).
data is enough. D2-D4 pass the data on at 4.0 V, enough for D5-D7.
The body is 5.6 mm tall: the front of the robot is lifted by the 7.5 mm ball caster or skid (lens about 2.25 mm above the floor)
PS1 = LEFT -> D2 (GPIO2/ADC), PS2 = CENTRE -> D1 (GPIO1/ADC), PS3 = RIGHT -> D0 (GPIO0/ADC) (seen from above, robot moving up the page)
internal pull-up, pressed = 0. R10: if START is pressed while D4 beeps, only 3.3 mA flows
GPIO16 (TX) / GPIO17 (RX) pull-up after reset + boot log / UART REPL -> no button and no motor input there.
1. POWER
5. LINE SENSORS 3 x LBR-127HLD (mount on the BOTTOM side, lens to the floor), 12 mm apart
rev.L5: U3 = AE-XC9306-5V0 (5.0 V from 2.5-5.5 V). C2 holds VIN_BB through short battery-contact gaps (D1 keeps the motors off it).
H/L fwd, L/H rev, H/H brake, L/L coast. Over-current (ISD) latches OFF:
GPIO15 = yellow user LED on the XIAO (on = 0), a 2nd indicator for free. BOOT / RESET buttons are on the XIAO.
IR LED: (3.3V - 1.2V - 0.1V) / 100 ohm = about 20 mA each. Q1 switches all LEDs (ambient light cancel). Photo transistor: 10k pull-up -> white = low voltage, black = high voltage
LARGE=L : small mode (2 motors, 2A/ch) MODE=L : IN/IN control
On pin headers the XIAO sits 2.5 mm above the board: its bare bottom test pads can not touch the tracks.
IN1/IN2 -> OUT1/OUT2 = LEFT motor, IN3/IN4 -> OUT3/OUT4 = RIGHT motor (+ = OUT4)
Reset state (ESP32-C6 datasheet): GPIO18-23 weak pull-up during reset, then floating;
A piezo passes no DC, so reading the button (input + pull-up)
Never solder a Li-ion cell to the XIAO's BAT pads on this robot (the AA cells feed the 5V pin through U3).
D2..D7 = PL9823 (NeoPixel type, 800 kHz, 24 bit per LED): D2-D4 left side (rear -> front, VDD = VLED_L),
2. MCU Seeed Studio XIAO ESP32C6 (on two 1x7 pin headers)
Why rev.L4: 2 motors starting / stalled pull 2-4 A and the AA cells sag to 2.5-3.3 V; the XIAO needs about 4 V on its 5V pin and reset.

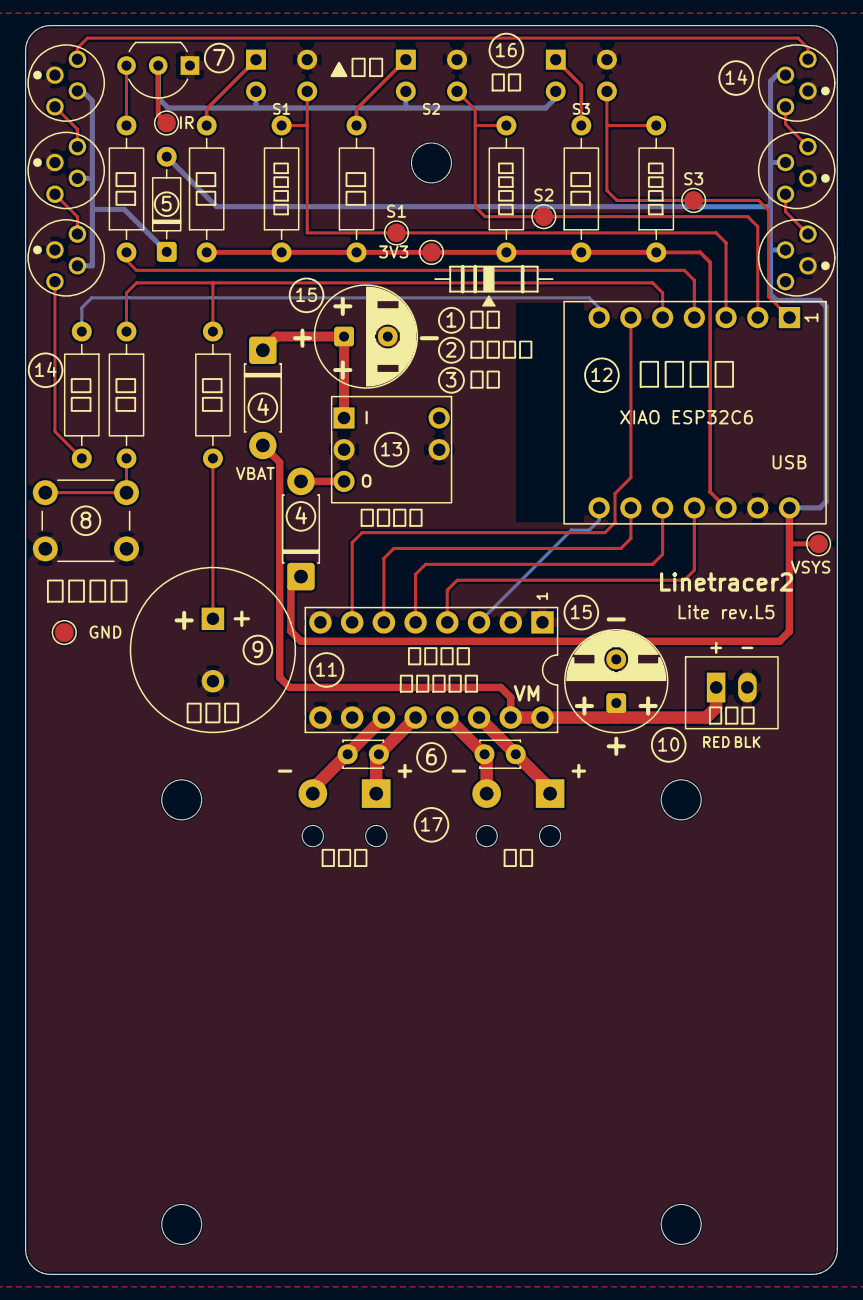
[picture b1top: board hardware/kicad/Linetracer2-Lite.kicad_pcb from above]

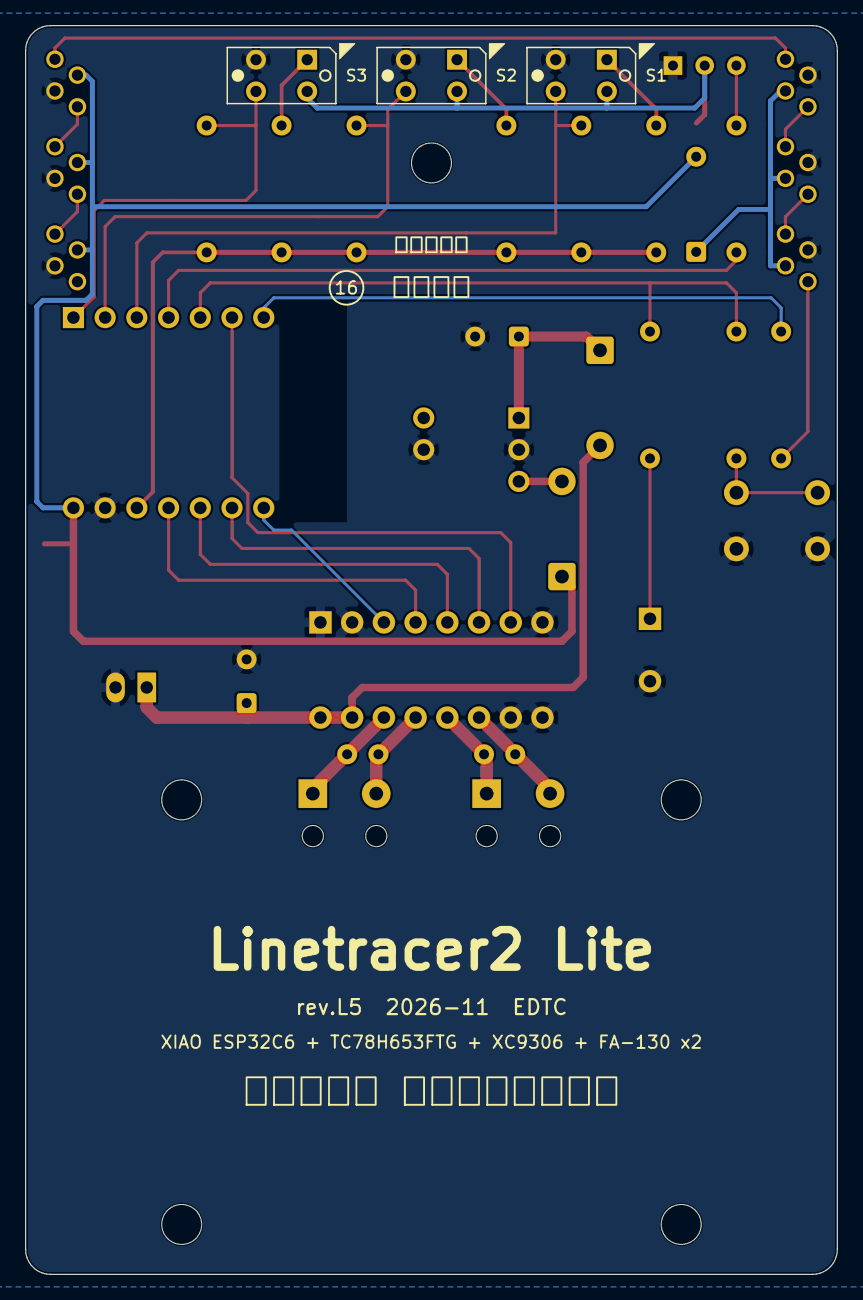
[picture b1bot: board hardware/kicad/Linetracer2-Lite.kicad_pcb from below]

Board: 2 copper layers, 65.0 x 100.0 mm, 47 parts (3 on the bottom side), 35 nets.

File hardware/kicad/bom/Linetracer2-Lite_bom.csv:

"Refs","Value","Footprint","Akizuki","Note","Qty"
"BZ1","piezo 13mm","Linetracer2:Buzzer_PKM13_P5.0","104118 (Murata PKM13EPYH4000-A0)","passive piezo, + on the square pad","1"
"C1,C2","470uF 16V","Capacitor_THT:CP_Radial_D8.0mm_P3.50mm","108426 (Rubycon 16WXA470MEFC 8x9)","hold-up: carries U3 through short gaps of the battery contacts,motor bulk capacitor, place near U2 VM","2"
"C3,C4","0.1uF (at motor)","Capacitor_THT:C_Disc_D3.0mm_W2.0mm_P2.50mm","113582 (10pcs)","","2"
"D1,D8","1N5819","Diode_THT:D_DO-41_SOD81_P7.62mm_Horizontal","117244 (10pcs)","OR diode: U3 can not feed the PC's USB port, USB 5 V can not feed U3,reverse battery: protects U3 and the XIAO; keeps the motors off C2","2"
"D2-D7","PL9823","Linetracer2:LED_PL9823_5mm","108411 (PL9823-F5)","","6"
"D9","1N4148","Diode_THT:D_DO-35_SOD27_P7.62mm_Horizontal","1N4148 (check the code)","level shift: the first LED runs 0.7 V lower","1"
"J1","BATTERY (AA x3, XH 2P)","Linetracer2:BatteryXH_2P","112247 (B2B-XH-A) / battery box 112243","red wire = + (pin 1)","1"
"M1","LEFT motor  FA-130RA","Linetracer2:MotorPads_2P_Relief","106437","","1"
"M2","RIGHT motor FA-130RA","Linetracer2:MotorPads_2P_Relief","106437","","1"
"PS1-PS3","LBR-127HLD","Linetracer2:LBR-127HLD","104500","","3"
"Q1","2SC1815-GR","Package_TO_SOT_THT:TO-92_Inline_Wide","117089","","1"
"R1-R3,R9","100","Resistor_THT:R_Axial_DIN0207_L6.3mm_D2.5mm_P10.16mm_Horizontal","125101 (100pcs)","","4"
"R4-R6","10k","Resistor_THT:R_Axial_DIN0207_L6.3mm_D2.5mm_P10.16mm_Horizontal","125103 (100pcs)","","3"
"R7,R10,R11","1k","Resistor_THT:R_Axial_DIN0207_L6.3mm_D2.5mm_P10.16mm_Horizontal","125102 (100pcs)","","3"
"SW1","START","Button_Switch_THT:SW_PUSH_6mm","108075","","1"
"U1","XIAO ESP32C6","Linetracer2:XIAO_ESP32C6_Header","129481 (Seeed Studio XIAO ESP32C6) + pin header 1x40 100167 (2 x 7 pins)","solder the XIAO on two 1x7 pin headers (cut from a 1x40 strip), then into the board","1"
"U2","AE-TC78H653FTG","Linetracer2:AE-TC78H653FTG","114746","uses the two 1x8 pin headers that come with the module","1"
"U3","AE-XC9306-5V0","Linetracer2:AE-XC9306-5V0","115775 (AE-XC9306-5V0, 5 V fixed, 2 thin 1x3 pin headers included)","pull the TRIM pin (across from O) out of its header: no hole on the board","1"

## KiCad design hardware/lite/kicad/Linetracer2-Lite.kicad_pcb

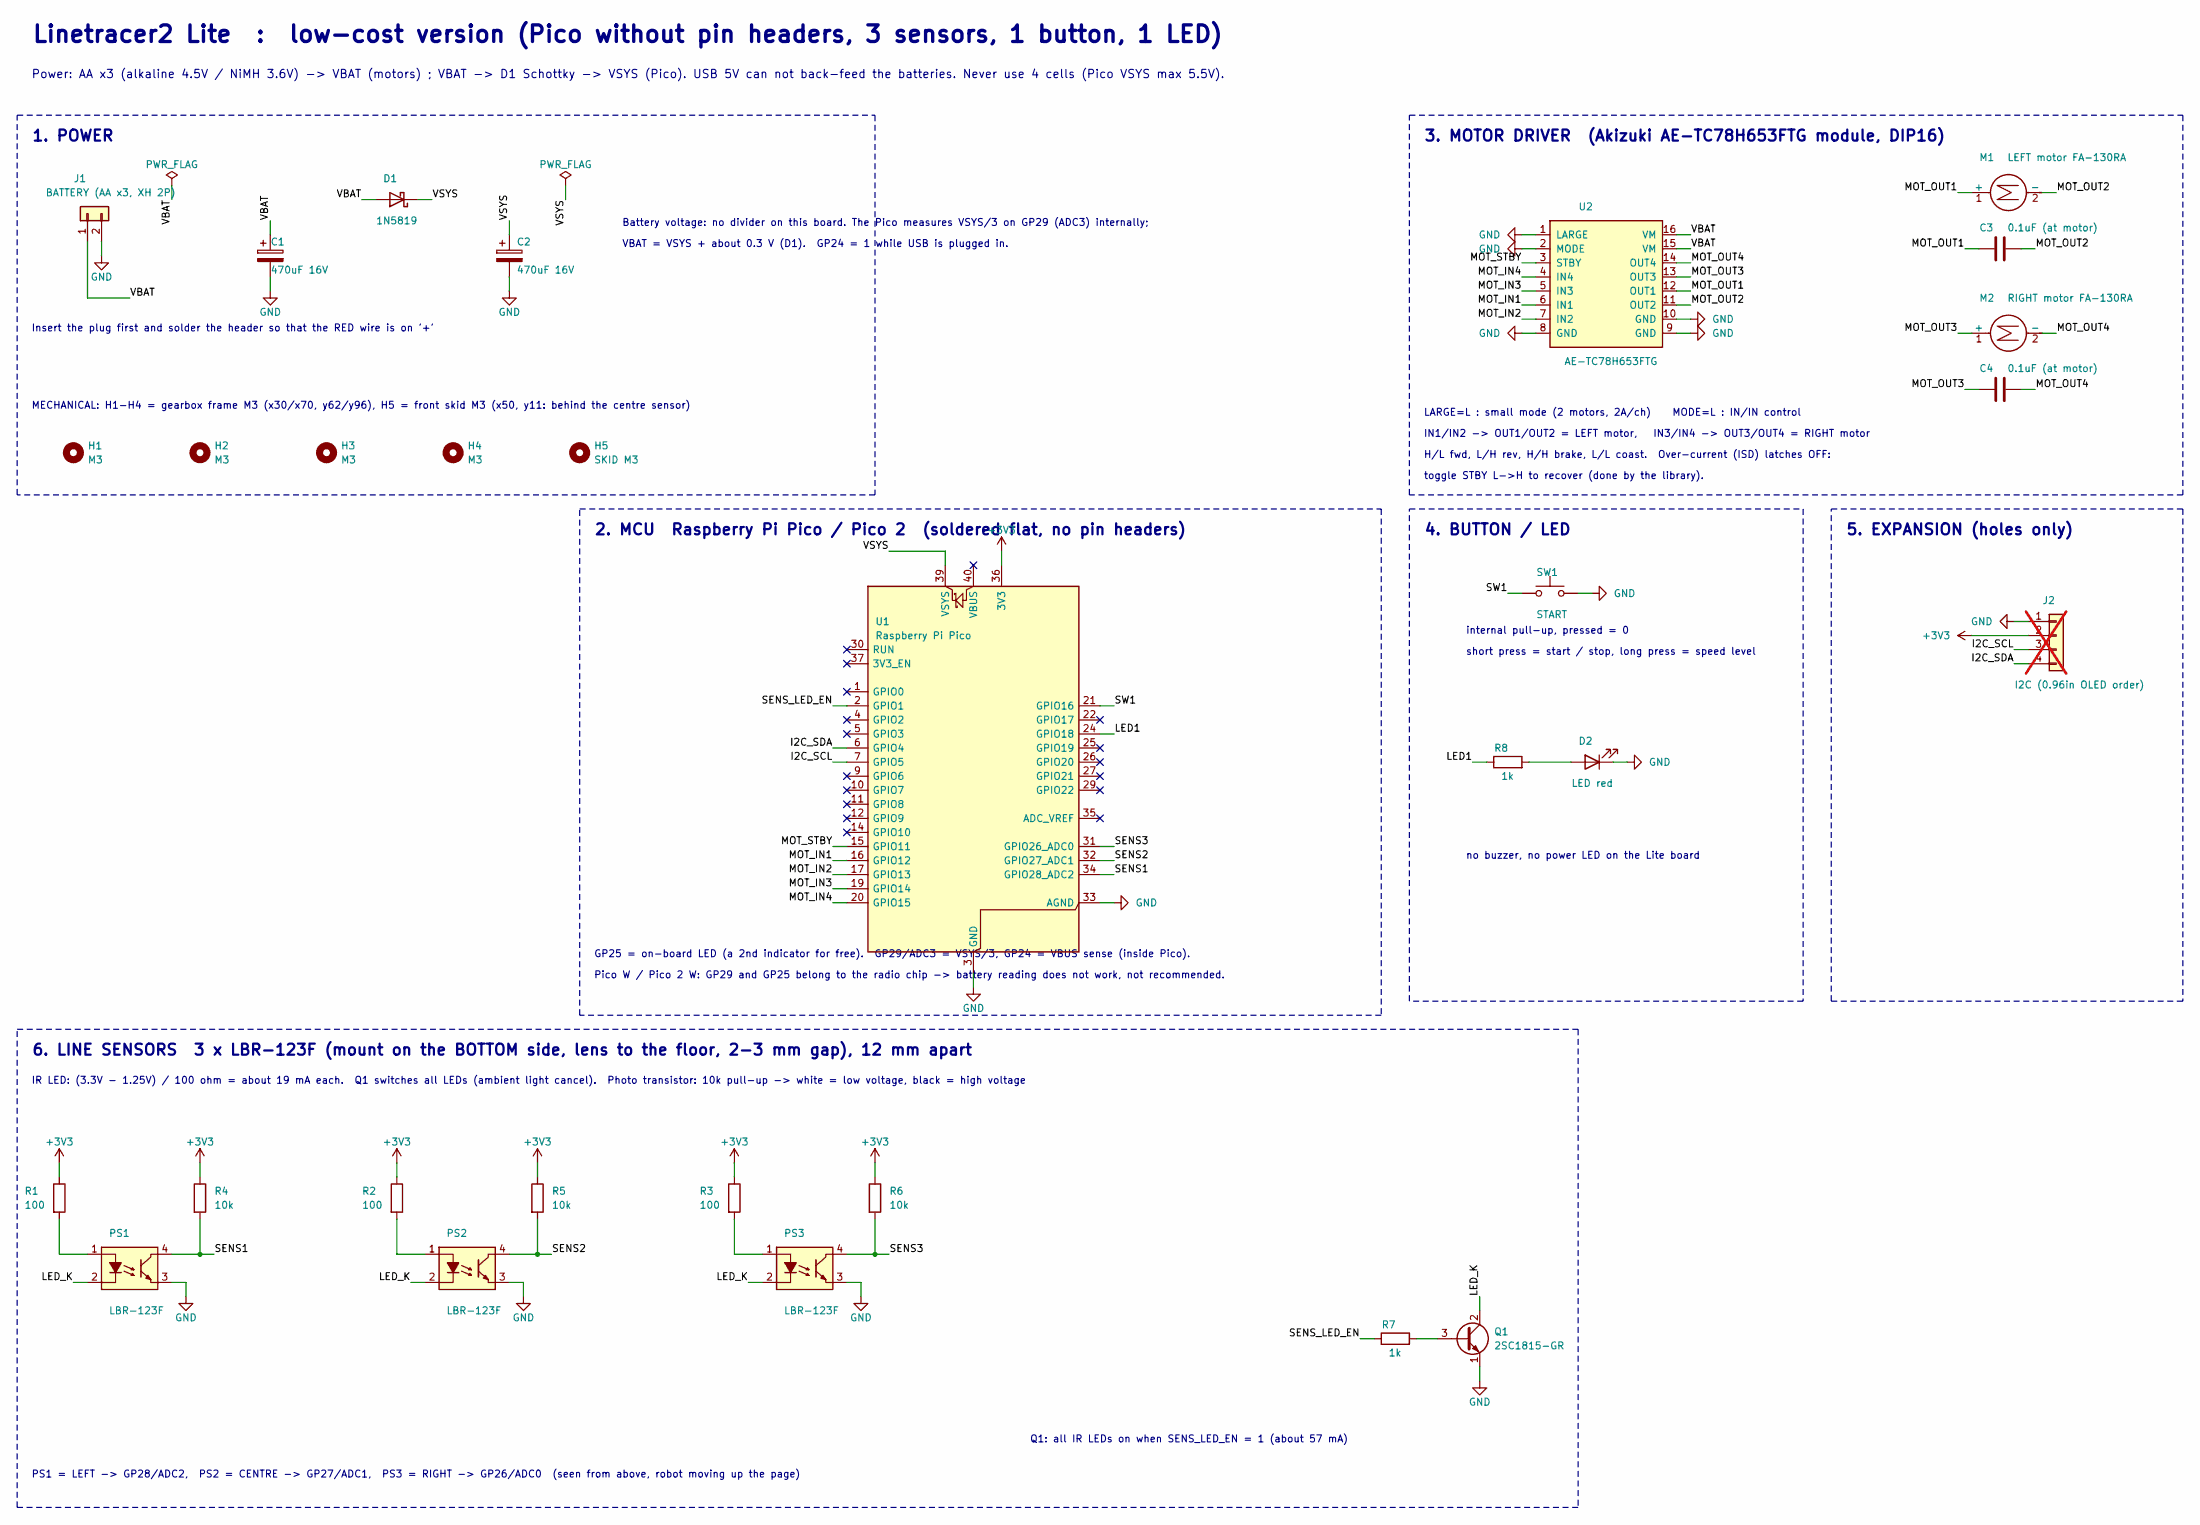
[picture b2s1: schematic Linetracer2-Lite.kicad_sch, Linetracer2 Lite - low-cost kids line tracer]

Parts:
C1, C2: 470uF 16V; CP_Radial_D8.0mm_P3.50mm
C3, C4: 0.1uF (at motor); C_Disc_D3.0mm_W2.0mm_P2.50mm
D1: 1N5819; D_DO-41_SOD81_P10.16mm_Horizontal
D2: LED red; LED_D3.0mm
H1, H2, H3, H4: M3; MountingHole_3.2mm_M3
H5: SKID M3; MountingHole_3.2mm_M3
J1: BATTERY (AA x3, XH 2P); BatteryXH_2P
J2: I2C (0.96in OLED order); PinHeader_1x04_P2.54mm_Vertical; not fitted
M1: LEFT motor FA-130RA; MotorPads_2P_Relief
M2: RIGHT motor FA-130RA; MotorPads_2P_Relief
PS1, PS2, PS3: LBR-123F
Q1: 2SC1815-GR; TO-92_Inline_Wide
R1, R2, R3: 100; R_Axial_DIN0207_L6.3mm_D2.5mm_P10.16mm_Horizontal
R4, R5, R6: 10k; R_Axial_DIN0207_L6.3mm_D2.5mm_P10.16mm_Horizontal
R7, R8: 1k; R_Axial_DIN0207_L6.3mm_D2.5mm_P10.16mm_Horizontal
SW1: START; SW_PUSH_6mm
U1: Raspberry Pi Pico; RaspberryPi_Pico_DirectSolder
U2: AE-TC78H653FTG

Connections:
+3V3: J2.2, R1.1, R2.1, R3.1, R4.1, R5.1, R6.1, U1.36 (3V3)
/I2C_SCL: J2.3, U1.7 (GPIO5)
/I2C_SDA: J2.4, U1.6 (GPIO4)
/LED1: R8.1, U1.24 (GPIO18)
/LED_K: PS1.2 (K), PS2.2 (K), PS3.2 (K), Q1.2 (C)
/MOT_IN1: U1.16 (GPIO12), U2.6 (IN1)
/MOT_IN2: U1.17 (GPIO13), U2.7 (IN2)
/MOT_IN3: U1.19 (GPIO14), U2.5 (IN3)
/MOT_IN4: U1.20 (GPIO15), U2.4 (IN4)
/MOT_OUT1: C3.1, M1.1 (+), U2.12 (OUT1)
/MOT_OUT2: C3.2, M1.2 (-), U2.11 (OUT2)
/MOT_OUT3: C4.1, M2.1 (+), U2.13 (OUT3)
/MOT_OUT4: C4.2, M2.2 (-), U2.14 (OUT4)
/MOT_STBY: U1.15 (GPIO11), U2.3 (STBY)
/SENS1: PS1.4 (C), R4.2, U1.34 (GPIO28_ADC2)
/SENS2: PS2.4 (C), R5.2, U1.32 (GPIO27_ADC1)
/SENS3: PS3.4 (C), R6.2, U1.31 (GPIO26_ADC0)
/SENS_LED_EN: R7.1, U1.2 (GPIO1)
/SW1: SW1.1, U1.21 (GPIO16)
/VBAT: C1.1, D1.2 (A), J1.1, U2.15 (VM), U2.16 (VM)
/VSYS: C2.1, D1.1 (K), U1.39 (VSYS)
GND: C1.2, C2.2, D2.1 (K), J1.2, J2.1, PS1.3 (E), PS2.3 (E), PS3.3 (E), Q1.1 (E), SW1.2, U1.3 (GND), U1.8 (GND), U1.13 (GND), U1.18 (GND), U1.23 (GND), U1.28 (GND), U1.33 (AGND), U1.38 (GND), U2.1 (LARGE), U2.2 (MODE), U2.8 (GND), U2.9 (GND), U2.10 (GND)
unnamed: D2.2 (A), R8.2
unnamed: PS1.1 (A), R1.2
unnamed: PS2.1 (A), R2.2
unnamed: PS3.1 (A), R3.2
unnamed: Q1.3 (B), R7.2

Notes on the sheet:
IN1/IN2 -> OUT1/OUT2 = LEFT motor, IN3/IN4 -> OUT3/OUT4 = RIGHT motor
Power: AA x3 (alkaline 4.5V / NiMH 3.6V) -> VBAT (motors) ; VBAT -> D1 Schottky -> VSYS (Pico). USB 5V can not back-feed the batteries. Never use 4 cells (Pico VSYS max 5.5V).
LARGE=L : small mode (2 motors, 2A/ch) MODE=L : IN/IN control
2. MCU Raspberry Pi Pico / Pico 2 (soldered flat, no pin headers)
Insert the plug first and solder the header so that the RED wire is on '+'
6. LINE SENSORS 3 x LBR-123F (mount on the BOTTOM side, lens to the floor, 2-3 mm gap), 12 mm apart
no buzzer, no power LED on the Lite board
Pico W / Pico 2 W: GP29 and GP25 belong to the radio chip -> battery reading does not work, not recommended.
1. POWER
MECHANICAL: H1-H4 = gearbox frame M3 (x30/x70, y62/y96), H5 = front skid M3 (x50, y11: behind the centre sensor)
5. EXPANSION (holes only)
Q1: all IR LEDs on when SENS_LED_EN = 1 (about 57 mA)
PS1 = LEFT -> GP28/ADC2, PS2 = CENTRE -> GP27/ADC1, PS3 = RIGHT -> GP26/ADC0 (seen from above, robot moving up the page)
Battery voltage: no divider on this board. The Pico measures VSYS/3 on GP29 (ADC3) internally;
4. BUTTON / LED
VBAT = VSYS + about 0.3 V (D1). GP24 = 1 while USB is plugged in.
GP25 = on-board LED (a 2nd indicator for free). GP29/ADC3 = VSYS/3, GP24 = VBUS sense (inside Pico).
H/L fwd, L/H rev, H/H brake, L/L coast. Over-current (ISD) latches OFF:
3. MOTOR DRIVER (Akizuki AE-TC78H653FTG module, DIP16)
IR LED: (3.3V - 1.25V) / 100 ohm = about 19 mA each. Q1 switches all LEDs (ambient light cancel). Photo transistor: 10k pull-up -> white = low voltage, black = high voltage
short press = start / stop, long press = speed level
Linetracer2 Lite : low-cost version (Pico without pin headers, 3 sensors, 1 button, 1 LED)
internal pull-up, pressed = 0
toggle STBY L->H to recover (done by the library).
